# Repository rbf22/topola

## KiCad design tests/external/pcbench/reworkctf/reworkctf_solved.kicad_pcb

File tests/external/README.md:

# External board fixtures

Third-party boards used as routing tests/benchmarks. Each directory keeps
the unrouted problem (`*.dsn`) next to its known-good routed solution for
comparison.

## `optoisolator_4n35/` — PCBench (MIT)

- Source: https://github.com/PCBench/PCBench →
  `PCBs/4N35-TTL-Serial-Optoisolator_4N35-TTL-Serial-Optoisolator`
- `optoisolator_4n35_solved.kicad_pcb` — upstream `processed.kicad_pcb`
  (contains the human routing; MIT per its `metadata.json`)
- `optoisolator_4n35.dsn` — Specctra DSN exported after deleting all
  tracks/vias
- `optoisolator_4n35_solved.dsn` — same export with routing kept
- Regenerate:
  ```bash
  PY=/Applications/KiCad/KiCad.app/Contents/Frameworks/Python.framework/Versions/Current/bin/python3
  $PY - <<'EOF'
  import pcbnew
  b = pcbnew.LoadBoard("optoisolator_4n35_solved.kicad_pcb")
  pcbnew.ExportSpecctraDSN(b, "optoisolator_4n35_solved.dsn")
  for t in list(b.GetTracks()):
      b.Remove(t)
  pcbnew.ExportSpecctraDSN(b, "optoisolator_4n35.dsn")
  EOF
  ```
  (`kicad-cli` ≥10 no longer has a `specctra-dsn` export subcommand; the
  pcbnew Python API is the alternative. `b.GetTracks()` misbehaves in some
  KiCad versions — stripping `(segment …)`/`(via …)` lines from the
  `.kicad_pcb` text works too.)

## `fasttest/` — Freerouting fixture

- Source: `Issue313-FastTest.dsn` from the freerouting fixture corpus
  (mirror: https://github.com/dilawar/dsn-parser `dsn-files/`).
  Freerouting fixtures are user-submitted issue reproductions under the
  freerouting repo's GPL — check before distributing.
- `fasttest_solved.dsn` — upstream file unchanged; its `(wiring …)` scope
  is the embedded solution (all `protect` type)
- `fasttest.dsn` — same file with an empty `(wiring)` scope (specctra-core
  requires the scope to exist); this is the routing problem
- Regenerate: replace the `(wiring …)` scope in `fasttest_solved.dsn` with
  `(wiring)`.

## `pcbench/` — PCBench corpus subset (MIT/permissive)

- Source: https://github.com/PCBench/PCBench (`PCBs/`), pinned commit
  `dec3be75cbdef74787625f9043c7391cd473bb64` — fetched by
  `scripts/fetch_corpora.sh` into the gitignored `bench/corpora-src/`.
- 16 boards selected from ~1180 for spread of layer count, net count and
  density — see `bench/corpus.tsv`. Only permissively licensed upstream
  boards (MIT / Apache-2.0 / BSD / CC0 / CC-BY / LGPL) are vendored;
  per-board license/author lives in each upstream `metadata.json`.
- `<slug>.dsn` is the routing problem (tracks stripped from
  `processed.kicad_pcb`), `<slug>_solved.dsn` the human reference
  routing; `.kicad_pcb` originals kept alongside.
- Regenerate: `ROW_FILTER=<slug> scripts/vendor_corpus.sh` (uses
  `scripts/kicad_to_dsn.py` under KiCad's pcbnew python; the board must
  load in the installed KiCad — a few PCBench boards are unloadable in
  KiCad 10 and were excluded during curation).

## `freerouting/` — freerouting fixture corpus subset (GPL)

- Source: `fixtures/` in https://github.com/freerouting/freerouting,
  pinned commit `1be66ad2797395f3a258a7f3b9b31c724a624867` — fetched by
  `scripts/fetch_corpora.sh` (sparse checkout).
- 15 boards selected from ~160 `IssueNNN-*.dsn` reproductions for
  diversity (2/4/6 layers, 24–764 nets, dense + sparse).
- `<slug>.dsn` is the original fixture with its `(wiring …)` scope
  emptied; `<slug>_solved.dsn` keeps the embedded freerouting solution.
- Regenerate: `ROW_FILTER=<slug> scripts/vendor_corpus.sh`
  (`scripts/strip_wiring.py` + `scripts/dsnutil.py` — also normalises
  the pcb name on line 1, renames empty class names, and ensures a
  `(wiring)` scope exists; see quirks below).
- License caveat still applies: fixtures are user submissions under the
  freerouting GPL umbrella — `GPL-3.0-only` in REUSE.toml; don't
  redistribute outside this repo without checking.

## Parser quirks hit while importing (kept for future imports)

- `specctra-core` learns `string_quote`/`space_in_quoted_tokens` from the
  `(parser …)` scope, which comes *after* the pcb name — a quoted pcb name
  containing spaces (e.g. `Issue103-Board-Unrouted.dsn`) fails to parse.
  Workaround: unquote/rename the name on line 1.
- Multi-path `(boundary …)` scopes (panelized boards, e.g.
  `Issue034-Green14SegLED.dsn`) are rejected — single path only.
- `(class` scopes with an empty name (`Issue179-*.dsn`) are rejected.
- `(wiring` is a required scope — strip contents, not the scope itself.

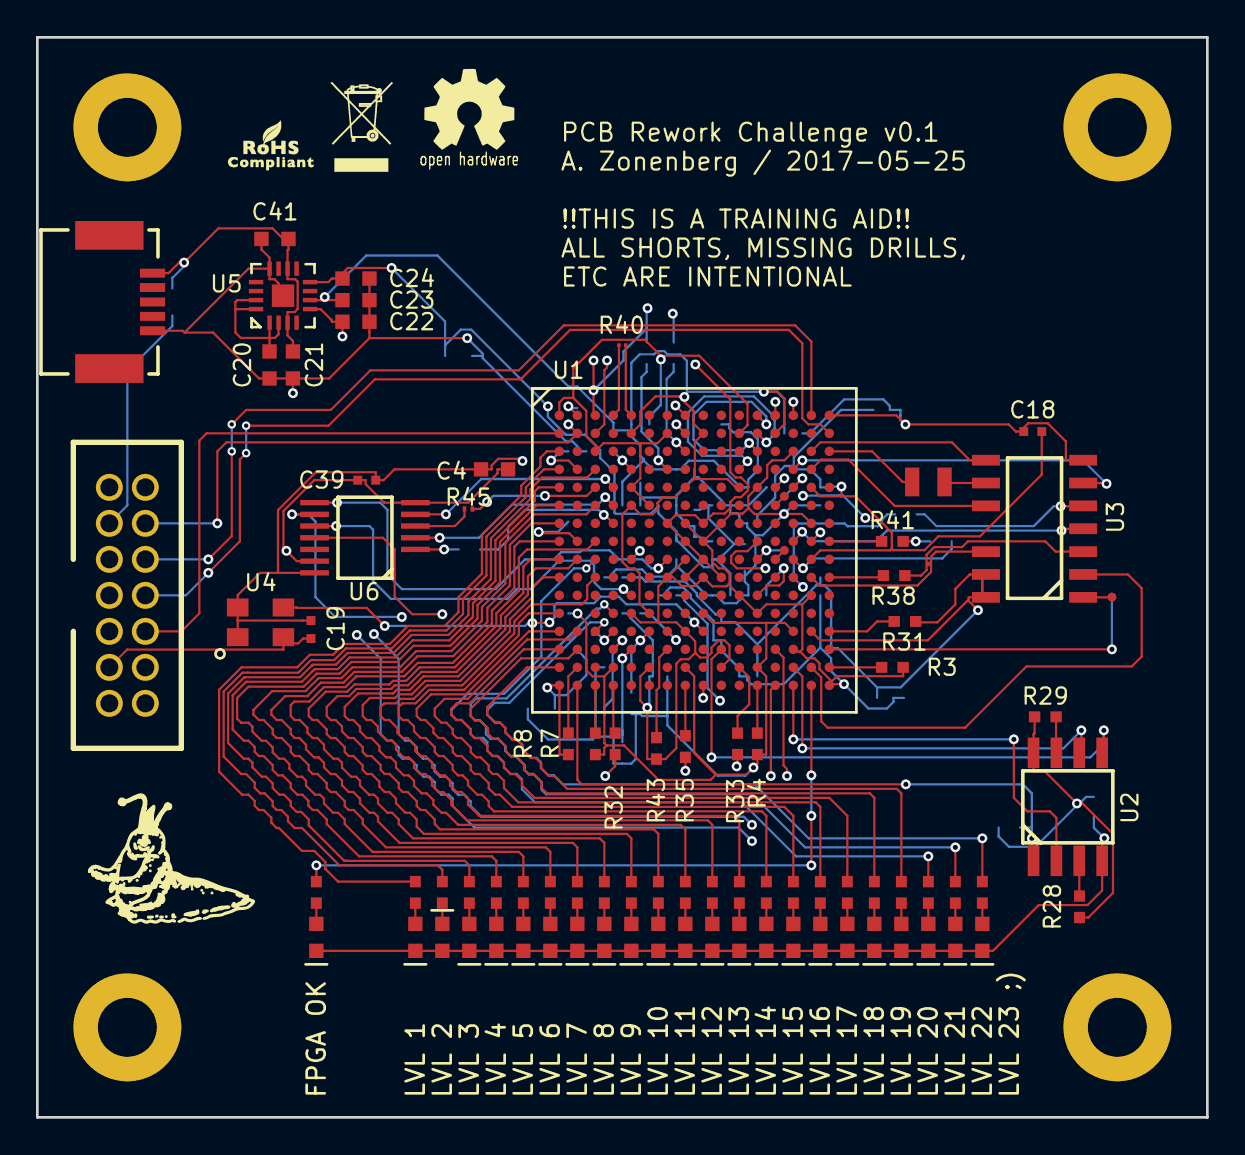
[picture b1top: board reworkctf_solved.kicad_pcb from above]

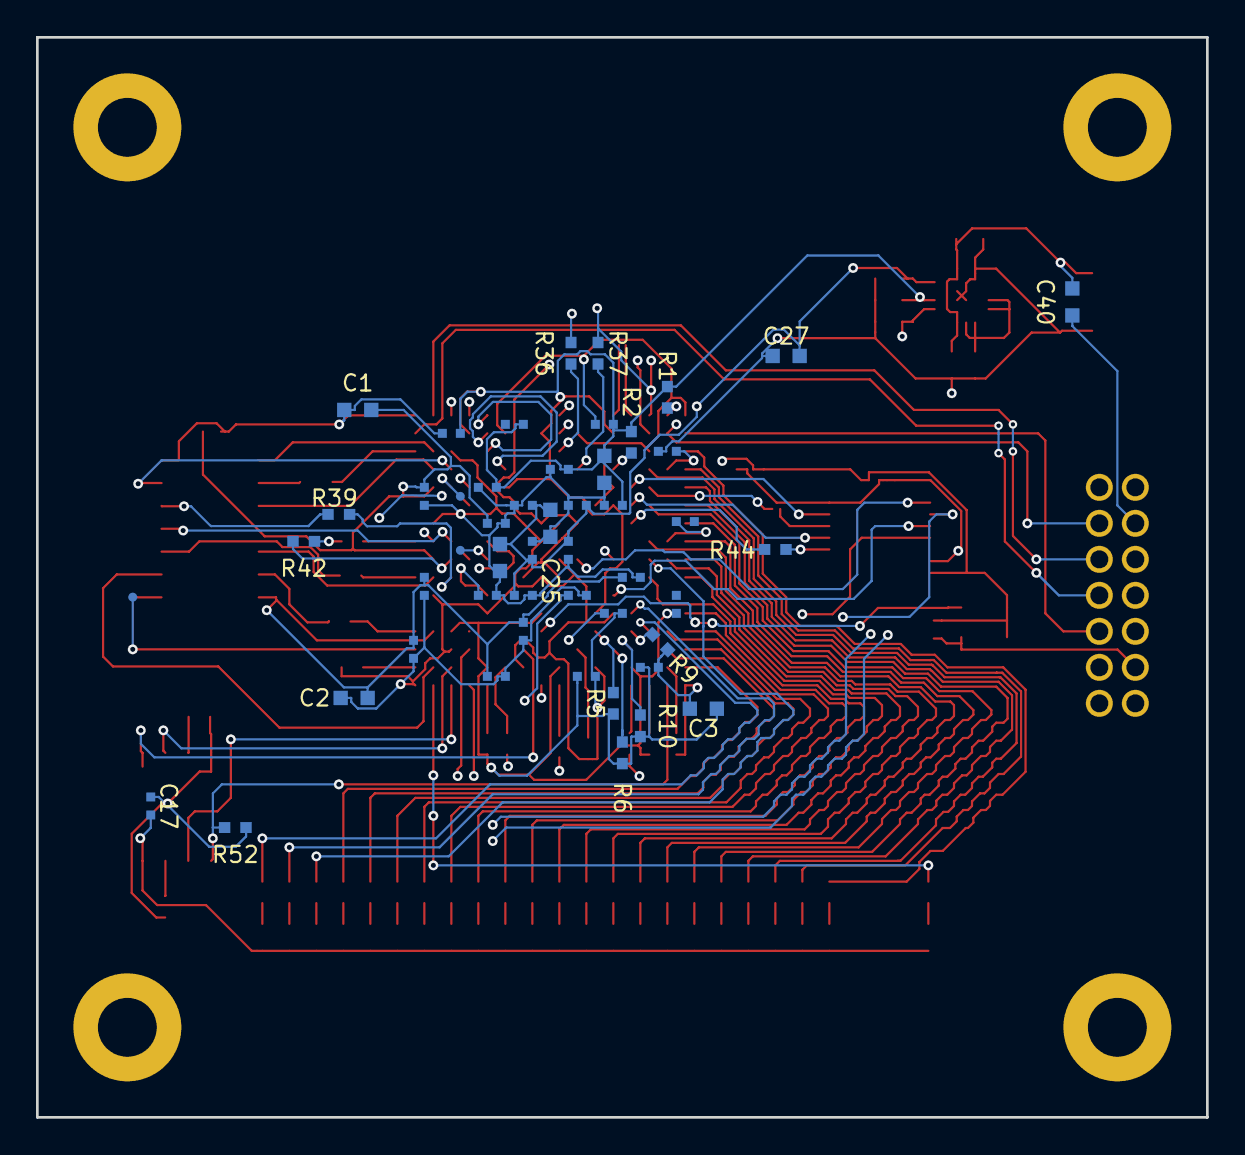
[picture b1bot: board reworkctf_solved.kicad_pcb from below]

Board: 4 copper layers, 65.0 x 60.0 mm, 135 parts (50 on the bottom side), 122 nets.

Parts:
C1, C2, C3, C4, C20, C21, C22, C23, C24, C25, C26, C27, C29, C40, C41: 4.7 uF; EIA_0603_CAP_NOSILK
C5, C6, C7, C8, C9, C10, C11, C12, C13, C14, C15, C16, C17, C18, C19, C28, C30, C31, C32, C33, C34, C35, C36, C37, C38, C39, C42, C43, C44, C45: 0.1 uF; EIA_0402_CAP_NOSILK
D1, D2, D3, D4, D5, D6, D7, D8, D9, D10, D11, D12, D13, D14, D15, D16, D17, D18, D19, D20, D21, D22, D23: GREEN; EIA_0603_LED
J1: XILINX_JTAG; XILINX_JTAG_PTH_MOLEX_0878311420
J2: UX60SX-MB-5ST; CONN_HIROSE_UX60S-MB-5ST_MINI_USB
LEVEL2_SHORT, LEVEL5_SHORT: TESTPOINT_BARETRACE_150UM
R1, R2, R3, R4, R5, R6, R7, R8, R9, R10, R28, R29, R52: 1K; EIA_0402_RES_NOSILK
R11, R12, R13, R14, R15, R16, R17, R18, R19, R20, R21, R22, R23, R24, R25, R26, R27, R46, R47, R48, R49, R50, R51: 470; EIA_0402_RES_NOSILK
R30: 0; EIA_0805_CAP_NOSILK
R31, R32, R33, R35, R36, R37, R38, R39, R41, R42, R43: 270; EIA_0402_RES_NOSILK
R40: 270; EIA_01005_RES_NOSILK
R44: 0; EIA_0402_RES_NOSILK
R45: 0; EIA_0201_RES_NOSILK
U1: XC3S50A-4FTG256C; BGA_256_17x17_FULLARRAY_1MM
U2: W25Q80BV; SOIC_8_3.9MM
U3: 74HC04; SOIC_14_3.9MM_NOPIN11
U4: 1 MHz; OSCILLATOR_3.2x2.5
U5: ADP322ACPZ-145-R7; QFN_16_0.5MM_3x3MM
U6: 74HC04; TSSOP_14_0.65MM_5p6MM_NOPINS_1_2
W1, W2, W3, W4, W5, W6: VIAPAD; TESTPOINT_SMT_0.5MM

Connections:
/1V2: C24.1, C25.1, C27.1, C29.1, C31.1, C33.1, C35.1, C36.1, C37.1, C38.1, U1.G7, U1.G9, U1.H8, U1.J9, U1.K8, U1.K10, U5.8
/2V5: C23.1, C26.1, C28.1, C30.1, C32.1, C34.1, C42.1, C43.1, C44.1, C45.1, J1.2, R1.1, R2.2, U1.B5, U1.B9, U1.B13, U1.E8, U1.E11, U1.F5, U1.L12, U1.M6, U5.6
/3V3: C1.1, C2.1, C3.1, C4.1, C5.1, C6.1, C7.1, C8.1, C9.1, C10.1, C11.1, C12.1, C13.1, C14.1, C15.1, C16.1, C17.2, C18.2, C19.2, C22.1, C39.2, R4.1, R5.1, R6.1, R7.1, R10.1, R28.2, R29.1, R52.2, U1.D2, U1.E15, U1.H2, U1.H12, U1.J5, U1.J15, U1.M2, U1.M9, U1.N14, U1.N15, U1.R4, U1.R8, U1.R12, U2.8, U3.14, U4.1, U4.4, U5.5, U6.14
/5V0: C21.1, C40.1, C41.1, J2.1, U5.3, U5.10
/CLK_1MHZ: U1.N9, U4.3
/FPGA_DONE: R27.2, U1.T15
/FPGA_RST_N: R1.2, U1.A2
/GND: C1.2, C2.2, C3.2, C4.2, C5.2, C6.2, C7.2, C10.2, C11.2, C12.2, C13.2, C14.2, C15.2, C16.2, C17.1, C18.1, C19.1, C20.2, C21.2, C22.2, C23.2, C24.2, C25.2, C26.2, C27.2, C28.2, C29.2, C30.2, C31.2, C32.2, C33.2, C35.2, C36.2, C37.2, C38.2, C39.1, C40.2, C41.2, C42.2, C43.2, C44.2, C45.2, D1.1, D2.2, D3.1, D4.1, D5.1, D6.1, D7.1, D8.1, D9.1, D10.1, D11.1, D12.1, D13.1, D14.1, D15.1, D16.1, D17.1, D18.1, D19.1, D20.1, D21.1, D22.1, D23.1, J1.3, J1.5, J1.7, J1.9, J1.11, J2.5, R3.2, R8.1, R9.1, R43.1, U1.A1, U1.A16, U1.B7, U1.B11, U1.C3, U1.C14, U1.E5, U1.E12, U1.F6, U1.G8, U1.G10, U1.G15, U1.H9, U1.J8, U1.K7, U1.K9, U1.L11, U1.L15, U1.M5, U1.M12, U1.N8, U1.P14, U1.R6, U1.R10, U1.T1, U1.T16, U2.4, U3.7, U4.2, U5.12, U5.PAD, U6.7, U6.13
/JTAG_TCK: J1.6, U1.A15
/JTAG_TDI: J1.10, U1.B1
/JTAG_TDO: J1.8, U1.B16
/JTAG_TMS: J1.4, U1.B2
/LEVEL1_OK: R11.2, U1.C1
/LEVEL1_SENSE: U1.K15, U3.12
/LEVEL1_TEST: R31.1, U3.13
/LEVEL2_OK: R12.2, U1.D1
/LEVEL3_OK: R13.2, U1.D3
/LEVEL3_SENSE: U1.D15, U3.10
/LEVEL4_OK: R14.2, U1.E1
/LEVEL4_SENSE: U1.C15, U3.8
/LEVEL4_TEST: R30.2, U3.9
/LEVEL5_OK: R15.2, U1.F1
/LEVEL5_SENSE: U1.H14, U3.4
/LEVEL5_TEST: R38.1, U3.3
/LEVEL6_OK: R16.2, U1.F3
/LEVEL6_SENSE: U1.D14, U3.6
/LEVEL6_TEST: R39.1, U3.5
/LEVEL7_OK: R17.2, U1.G1
/LEVEL7_TEST_N: U1.A12, U1.C12
/LEVEL7_TEST_P: U1.B12, U1.D11
/LEVEL8_OK: R18.2, U1.H1
/LEVEL9_OK: R19.2, U1.H3
/LEVEL9_SENSE: R40.2, U1.A5
/LEVEL9_TEST: R40.1, U1.A4
/LEVEL10_OK: R20.2, U1.J1
/LEVEL10_SENSE: U1.F4, U6.4
/LEVEL10_TEST: R44.2, U1.G4
/LEVEL11_OK: R21.2, U1.J2
/LEVEL11_SENSE: U1.E4, U6.6
/LEVEL11_TEST: R45.2, U1.E3
/LEVEL12_OK: R22.2, U1.K1
/LEVEL12_SENSE: U1.R15, U3.2
/LEVEL12_TEST: U1.P16, W5.1
/LEVEL12_TEST_FLOAT: U3.1, W6.1
/LEVEL13_OK: R23.2, U1.K3
/LEVEL13_TEST_A: R36.1, U1.B3
/LEVEL13_TEST_B: R37.1, U1.A3
/LEVEL14_OK: R24.2, U1.M1
/LEVEL14_SENSE: U1.J7, U6.8
/LEVEL14_TEST: U1.T9, U6.9
/LEVEL15_OK: R25.2, U1.N1
/LEVEL15_TEST_N: U1.A8, U1.A13
/LEVEL15_TEST_P: U1.A14, U1.B8
/LEVEL16_OK: R26.2, U1.N2
/LEVEL16_TEST_A: R32.1, U1.T13
/LEVEL16_TEST_B: R33.1, U1.P13
/LEVEL17_OK: R46.2, U1.P1
/LEVEL17_TEST: R43.2, U1.P7
/LEVEL18_OK: R47.2, U1.P2
/LEVEL18_SENSE: U1.J12, W1.1
/LEVEL18_TEST: U1.J13, W3.1
/LEVEL19_OK: R48.2, U1.R1
/LEVEL19_SENSE: R42.1, U1.J14
/LEVEL19_TEST: R41.2, R42.2, U1.E13, U1.H15
/LEVEL20_OK: R49.2, U1.J3
/LEVEL21_OK: R50.2, U1.M4
/LEVEL21_SENSE: U1.L5, U6.10
/LEVEL21_TEST: R35.1, U6.11
/LEVEL22_OK: R51.2, U1.N3
/LEVEL22_SENSE: U1.E14, W2.1
/LEVEL22_TEST: U1.F13, W4.1
/SPI_CS_N: R52.1, U1.T2, U2.1
/SPI_MISO: U1.T14, U2.2
/SPI_MOSI: U1.P10, U2.5
/SPI_SCK: U1.R14, U2.6
/VBIAS: C20.1, U5.1, U5.2, U5.15, U5.16
unnamed: D1.2, R11.1
unnamed: D2.1, R12.1
unnamed: D3.2, R13.1
unnamed: D4.2, R14.1
unnamed: D5.2, R15.1
unnamed: D6.2, R16.1
unnamed: D7.2, R17.1
unnamed: D8.2, R18.1
unnamed: D9.2, R19.1
unnamed: D10.2, R20.1
unnamed: D11.2, R21.1
unnamed: D12.2, R22.1
unnamed: D13.2, R23.1
unnamed: D14.2, R24.1
unnamed: D15.2, R25.1
unnamed: D16.2, R26.1
unnamed: D17.2, R27.1
unnamed: D18.2, R46.1
unnamed: D19.2, R47.1
unnamed: D20.2, R48.1
unnamed: D21.2, R49.1
unnamed: D22.2, R50.1
unnamed: D23.2, R51.1
unnamed: R2.1, U1.D5
unnamed: R3.1, U1.R16
unnamed: R4.2, U1.T12
unnamed: R5.2, U1.N6
unnamed: R6.2, U1.P5
unnamed: R7.2, U1.T3
unnamed: R8.2, U1.R2
unnamed: R9.2, U1.N4
unnamed: R10.2, U1.P4
unnamed: R28.1, U2.3
unnamed: R29.2, U2.7
unnamed: R30.1, U1.C16
unnamed: R31.2, U1.N16
unnamed: R32.2, U1.T4
unnamed: R33.2, U1.R11
unnamed: R35.2, U1.T8
unnamed: R36.2, U1.C8
unnamed: R37.2, U1.D7
unnamed: R38.2, U1.K16
unnamed: R39.2, U1.K14
unnamed: R41.1, U1.H16
unnamed: R44.1, U6.3
unnamed: R45.1, U6.5
